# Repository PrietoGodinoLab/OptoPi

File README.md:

# OptoPi

### OptoPi Overview

Here, we present OptoPi, an open source, affordable (~ £600), behavioural arena with accompanying multi-animal tracking software. The system features highly customisable and reproducible visible and infrared illumination and allows for temporally precise optogenetic stimulation. OptoPi acquires images using a Raspberry Pi camera, features motorised LED-based illumination, Arduino control, as well as spectrum and irradiance monitoring to fine-tune
illumination conditions with real time feedback.

Our open-source software (BIO) can be used to simultaneously track multiple animals while accurately keeping individual animal’s identity both in on-line and off-line modes. 

## BIO

For animal tracking we utilise and recommend BIO created by Joost de Folter. Currently, we use the [v1.7.6 release](https://github.com/folterj/BioImageOperation/releases/tag/v1.7.6). For the latest, actively maintained BIO repository see [BIO](https://github.com/folterj/BioImageOperation).

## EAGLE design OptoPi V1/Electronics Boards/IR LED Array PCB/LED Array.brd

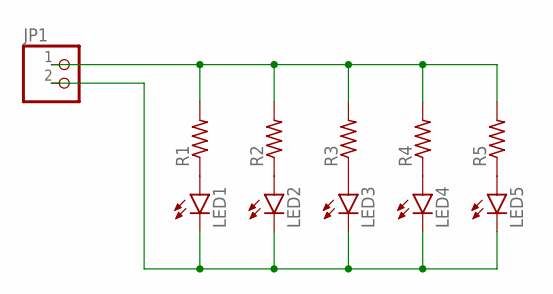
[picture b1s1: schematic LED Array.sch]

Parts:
JP1: PINHD-1X2; 1X02
LED1, LED2, LED3, LED4, LED5: LED3MM
R1, R2, R3, R4, R5: R-US_0207/12; 0207/12

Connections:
unnamed: LED1.A, R1.1
unnamed: LED3.A, R3.1
unnamed: LED2.A, R2.1
unnamed: LED4.A, R4.1
unnamed: JP1.2, LED1.K (C), LED2.K (C), LED3.K (C), LED4.K (C), LED5.K (C)
unnamed: JP1.1, R1.2, R2.2, R3.2, R4.2, R5.2
unnamed: LED5.A, R5.1

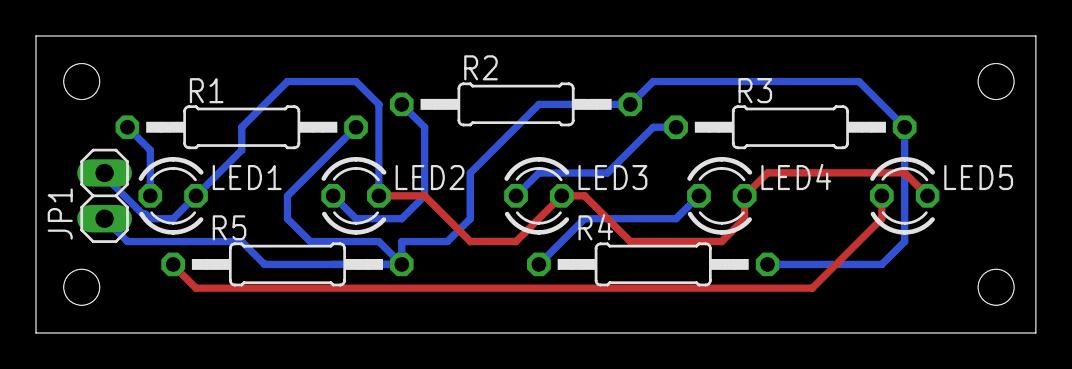
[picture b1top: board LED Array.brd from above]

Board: 2 copper layers, 55.5 x 16.5 mm, 11 parts (0 on the bottom side), 7 nets.

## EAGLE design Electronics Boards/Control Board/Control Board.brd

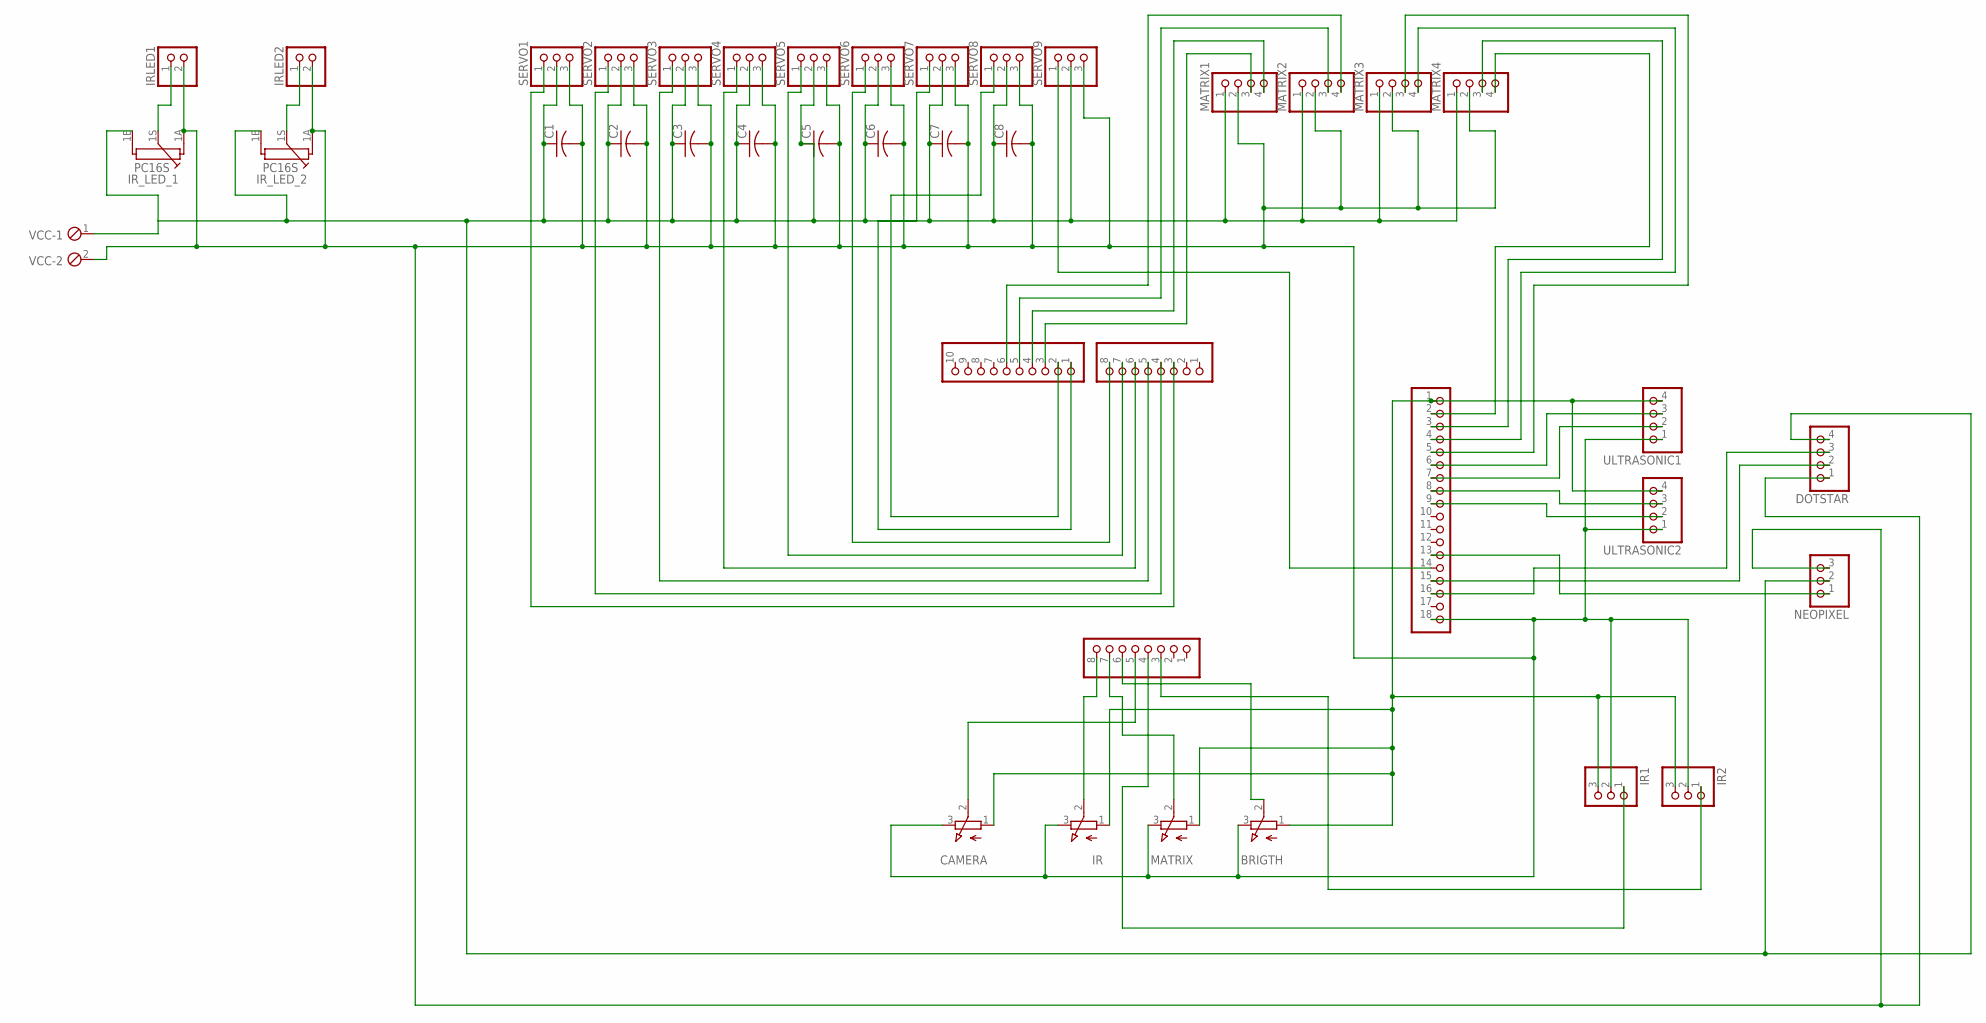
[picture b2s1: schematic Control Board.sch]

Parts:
BRIGTH: 3RP/1610N
C1, C2, C3, C4, C5, C6, C7, C8: C-US050-030X075; C050-030X075
CAMERA: 3RP/1610N
DOTSTAR: PINHD-1X4; 1X04
IR: 3RP/1610N
IR1, IR2: PINHD-1X3; 1X03
IRLED1, IRLED2: PINHD-1X2; 1X02
IR_LED_1, IR_LED_2: PC16S
MATRIX: 3RP/1610N
MATRIX1, MATRIX2, MATRIX3, MATRIX4: PINHD-1X4; 1X04
MEGABOTTOMCENTER: PINHD-1X8; 1X08
MEGALATERAL: PINHD-1X18; 1X18
MEGATOPCENTER: PINHD-1X8; 1X08
MEGATOPLEFT: PINHD-1X10_ARD; 1X10
NEOPIXEL: PINHD-1X3; 1X03
SERVO1, SERVO2, SERVO3, SERVO4, SERVO5, SERVO6, SERVO7, SERVO8, SERVO9: PINHD-1X3; 1X03
ULTRASONIC1, ULTRASONIC2: PINHD-1X4; 1X04
VCC: MPT2; 2POL254

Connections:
unnamed: MATRIX1.3, MEGATOPLEFT.3
unnamed: IR.2 (S), MEGABOTTOMCENTER.8
unnamed: MATRIX.2 (S), MEGABOTTOMCENTER.7
unnamed: BRIGTH.2 (S), MEGABOTTOMCENTER.6
unnamed: BRIGTH.1 (A), CAMERA.1 (A), IR.1 (A), IR1.3, IR2.3, MATRIX.1 (A), MEGALATERAL.1, ULTRASONIC1.4, ULTRASONIC2.4
unnamed: MEGALATERAL.7, ULTRASONIC1.2
unnamed: MEGALATERAL.6, ULTRASONIC1.3
unnamed: MEGALATERAL.8, ULTRASONIC2.3
unnamed: MEGALATERAL.9, ULTRASONIC2.2
unnamed: CAMERA.2 (S), MEGABOTTOMCENTER.5
unnamed: MATRIX1.4, MEGATOPLEFT.4
unnamed: MATRIX2.3, MEGATOPLEFT.5
unnamed: MATRIX2.4, MEGATOPLEFT.6
unnamed: MATRIX3.3, MEGALATERAL.5
unnamed: MATRIX3.4, MEGALATERAL.4
unnamed: MATRIX4.3, MEGALATERAL.3
unnamed: MATRIX4.4, MEGALATERAL.2
unnamed: DOTSTAR.2, MEGALATERAL.15
unnamed: IRLED2.1, IR_LED_2.1S
unnamed: IR1.1, MEGABOTTOMCENTER.4
unnamed: IR2.1, MEGABOTTOMCENTER.3
unnamed: MEGALATERAL.13, NEOPIXEL.1
unnamed: DOTSTAR.3, MEGALATERAL.16
unnamed: MEGALATERAL.14, SERVO9.1
unnamed: C1.1, C2.1, C3.1, C4.1, C5.1, C6.1, C7.1, C8.1, DOTSTAR.4, IR_LED_1.1E, IR_LED_2.1E, MATRIX1.1, MATRIX2.1, MATRIX3.1, MATRIX4.1, NEOPIXEL.2, SERVO1.2, SERVO2.2, SERVO3.2, SERVO4.2, SERVO5.2, SERVO6.2, SERVO7.2, SERVO8.2, SERVO9.2, VCC.1
unnamed: BRIGTH.3 (E), C1.2, C2.2, C3.2, C4.2, C5.2, C6.2, C7.2, C8.2, CAMERA.3 (E), DOTSTAR.1, IR.3 (E), IR1.2, IR2.2, IRLED1.2, IRLED2.2, IR_LED_1.1A, IR_LED_2.1A, MATRIX.3 (E), MATRIX1.2, MATRIX2.2, MATRIX3.2, MATRIX4.2, MEGALATERAL.18, NEOPIXEL.3, SERVO1.3, SERVO2.3, SERVO3.3, SERVO4.3, SERVO5.3, SERVO6.3, SERVO7.3, SERVO8.3, SERVO9.3, ULTRASONIC1.1, ULTRASONIC2.1, VCC.2
unnamed: MEGATOPCENTER.3, SERVO1.1
unnamed: MEGATOPCENTER.4, SERVO2.1
unnamed: MEGATOPCENTER.5, SERVO3.1
unnamed: MEGATOPCENTER.6, SERVO4.1
unnamed: MEGATOPLEFT.1, SERVO7.1
unnamed: MEGATOPCENTER.7, SERVO5.1
unnamed: MEGATOPCENTER.8, SERVO6.1
unnamed: MEGATOPLEFT.2, SERVO8.1
unnamed: IRLED1.1, IR_LED_1.1S

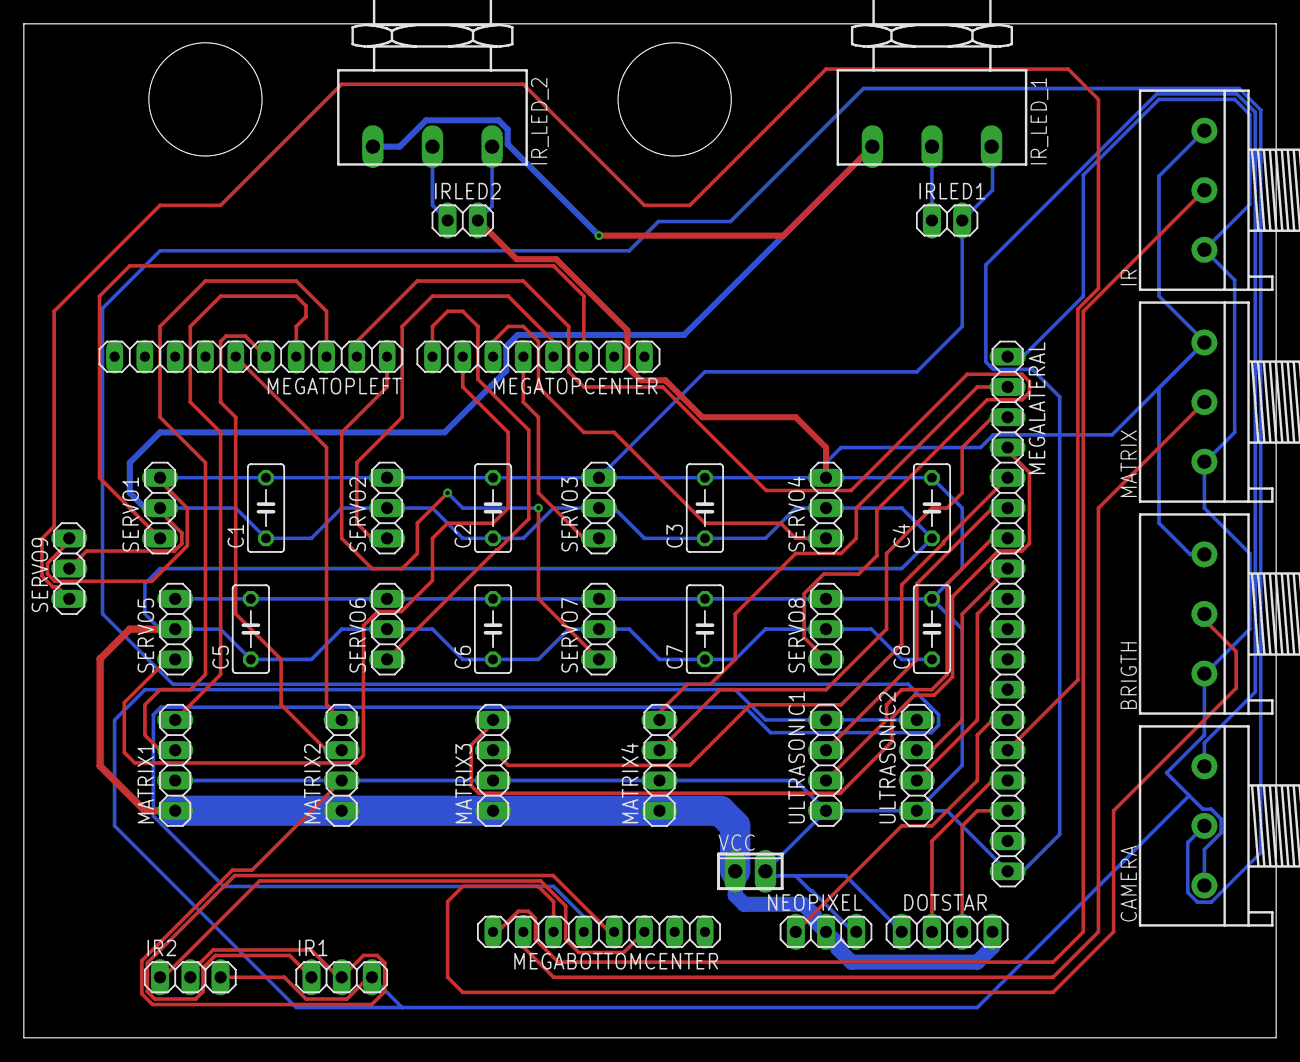
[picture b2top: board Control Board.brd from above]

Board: 2 copper layers, 105.1 x 85.1 mm, 40 parts (0 on the bottom side), 35 nets.

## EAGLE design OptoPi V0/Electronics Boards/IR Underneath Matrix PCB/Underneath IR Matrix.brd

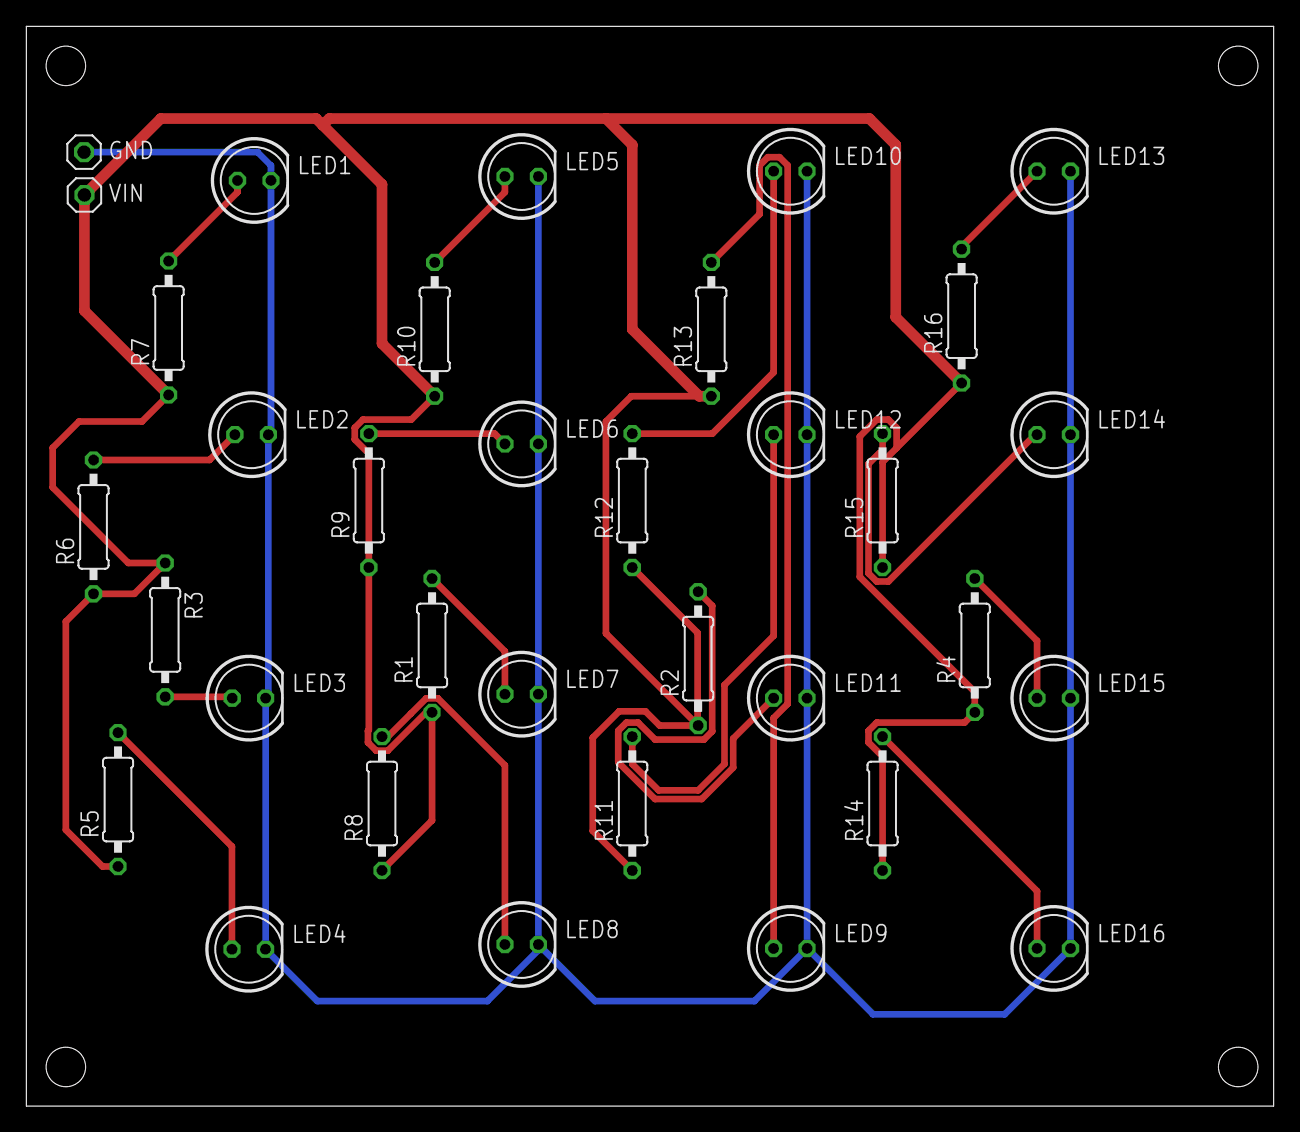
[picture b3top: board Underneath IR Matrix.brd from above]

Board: 2 copper layers, 94.7 x 82.0 mm, 34 parts (0 on the bottom side), 18 nets.

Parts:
GND: 1X01
LED1, LED2, LED3, LED4, LED5, LED6, LED7, LED8, LED9, LED10, LED11, LED12, LED13, LED14, LED15, LED16: LED5MM
R1, R2, R3, R4, R5, R6, R7, R8, R9, R10, R11, R12, R13, R14, R15, R16: 100; 0207/10
VIN: 1X01

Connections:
unnamed: LED5.A, R10.2
unnamed: LED6.A, R9.2
unnamed: LED4.A, R5.2
unnamed: LED8.A, R8.2
unnamed: LED7.A, R1.2
unnamed: LED1.A, R7.2
unnamed: LED2.A, R6.2
unnamed: LED12.A, R11.2
unnamed: GND.1, LED1.K, LED2.K, LED3.K, LED4.K, LED5.K, LED6.K, LED7.K, LED8.K, LED9.K, LED10.K, LED11.K, LED12.K, LED13.K, LED14.K, LED15.K, LED16.K
unnamed: R1.1, R2.1, R3.1, R4.1, R5.1, R6.1, R7.1, R8.1, R9.1, R10.1, R11.1, R12.1, R13.1, R14.1, R15.1, R16.1, VIN.1
unnamed: LED15.A, R4.2
unnamed: LED3.A, R3.2
unnamed: LED9.A, R13.2
unnamed: LED10.A, R12.2
unnamed: LED11.A, R2.2
unnamed: LED13.A, R16.2
unnamed: LED14.A, R15.2
unnamed: LED16.A, R14.2

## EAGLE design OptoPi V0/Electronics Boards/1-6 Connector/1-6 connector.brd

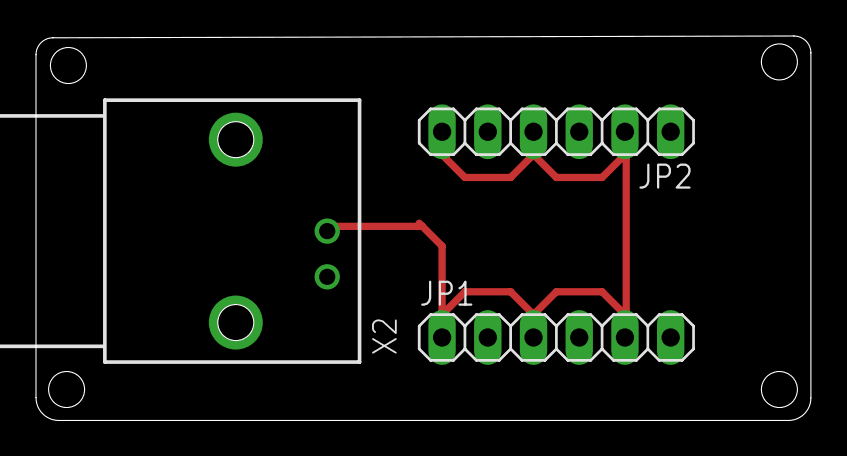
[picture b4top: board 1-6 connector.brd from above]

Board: 2 copper layers, 43.0 x 21.4 mm, 3 parts (0 on the bottom side), 2 nets.

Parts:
JP1, JP2: 1X06
X2: 1-227161-0; AMP_227161

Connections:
GND: JP1.2, JP1.4, JP1.6, JP2.1, JP2.3, JP2.5, X2.2
unnamed: JP1.1, JP1.3, JP1.5, JP2.2, JP2.4, JP2.6, X2.1

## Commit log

2021-12-06 RGB diffuser files
2022-01-09 Spectrometer data
2022-02-18 Thorlabs spectrum data
2022-06-28 Belt tensioner update
2022-06-28 Supplementary update
2022-06-30 uploading larger video to supplementary
2022-06-30 updating
2022-06-30 uploading larger video, hopefully git will not stick this time...
2022-06-30 serious synch problems wit problems with larger vids
2022-06-30 uploading example bioscript and visual_distortion_correction script
2022-06-30 updating visual distortion correction code
2022-09-12 Belt tensioner V2
2022-10-07 V1 folder
2022-11-30 PCBs update
2022-12-01 Electronic board adaptors
2022-12-08 ISR code
2022-12-09 OptoPi V1
2023-02-14 Add files via upload
    uploading simple python script as a proof of principle using the ISR mode
